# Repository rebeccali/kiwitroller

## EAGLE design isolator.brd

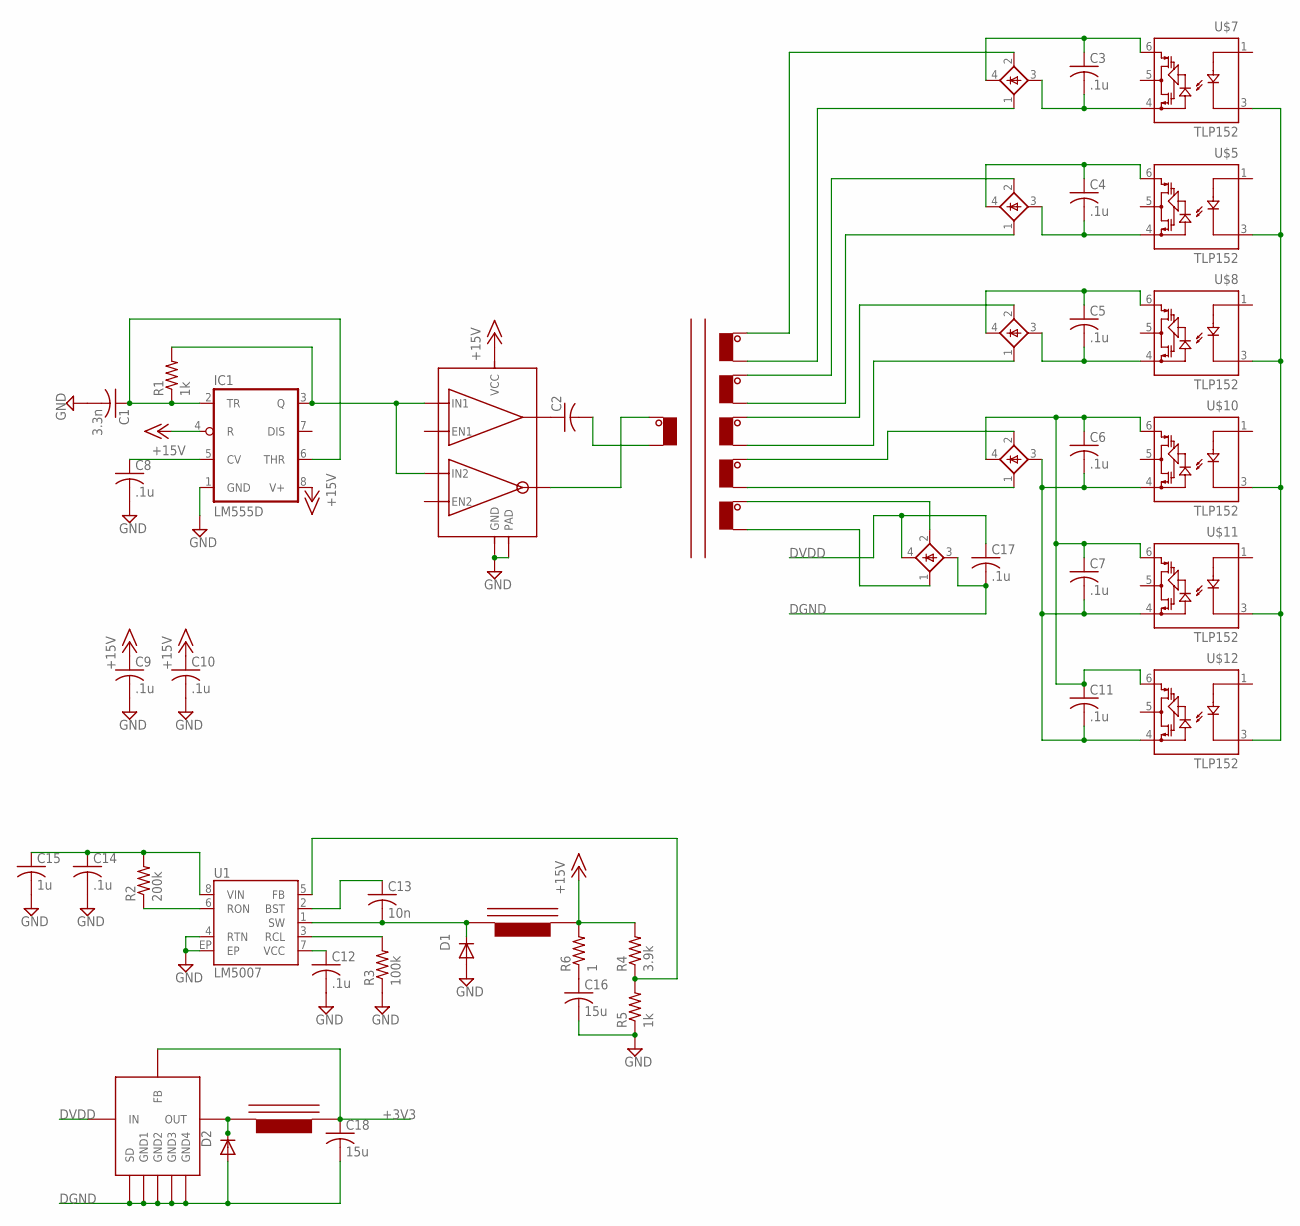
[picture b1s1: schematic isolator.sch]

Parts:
C1: 3.3n; C0805K
C2: C-USC0805K; C0805K
C3, C4, C5, C6, C7, C8, C9, C10, C11, C12, C14, C17: .1u; C0805K
C13: 10n; C0805K
C15: 1u; C0805K
C16, C18: 15u; C0805K
D1, D2: B170-13-F; DO214AC
IC1: LM555D; SO08
R1, R5: 1k; M0805
R2: 200k; M0805
R3: 100k; M0805
R4: 3.9k; M0805
R6: 1; M0805
U1: LM5007; MSOP-8-EP
U$1: HP1
U$2: UCC27525DGN; HTSSOP8DGN
U$3, U$4, U$6, U$9, U$14: BAS4002A; SOT-143
U$5, U$7, U$8, U$10, U$11, U$12: TLP152; DIP5-SMD
U$13, U$16: SRN6045-101M; SRN6045
U$15: AP1509; SO8

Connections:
+3V3: C18.1, U$15.3 (FB), U$16.P$2; also elsewhere on the board
+15V: C9.1, C10.1, IC1.4 (R), IC1.8 (V+), R4.2, R6.2, U$2.6 (VCC), U$13.P$2
DGND: C17.2, C18.2, D2.A, U$5.3 (LED-), U$7.3 (LED-), U$8.3 (LED-), U$10.3 (LED-), U$11.3 (LED-), U$12.3 (LED-), U$14.3 (-), U$15.4 (SD), U$15.5 (GND1), U$15.6 (GND2), U$15.7 (GND3), U$15.8 (GND4); also elsewhere on the board
DVDD: C17.1, U$14.4 (+), U$15.1 (IN)
E1: C3.2, U$3.3 (-), U$7.4 (GND); also elsewhere on the board
E2: C4.2, U$4.3 (-), U$5.4 (GND); also elsewhere on the board
E3: C5.2, U$6.3 (-), U$8.4 (GND); also elsewhere on the board
GND: C1.2, C8.2, C9.2, C10.2, C12.2, C14.2, C15.2, C16.2, D1.A, IC1.1 (GND), R3.1, R5.1, U1.4 (RTN), U1.EP, U$2.3 (GND), U$2.EXP (PAD); also elsewhere on the board
IN1: U$7.1 (LED+); also elsewhere on the board
IN2: U$5.1 (LED+); also elsewhere on the board
IN3: U$8.1 (LED+); also elsewhere on the board
IN4: U$10.1 (LED+); also elsewhere on the board
IN5: U$11.1 (LED+); also elsewhere on the board
IN6: U$12.1 (LED+); also elsewhere on the board
unnamed: U$1.P$3 (3B), U$3.1 (AC1)
unnamed: C3.1, U$3.4 (+), U$7.6 (VDD)
unnamed: C2.1, U$2.7 (OUT1)
unnamed: U$1.P$4 (1A), U$2.5 (OUT2)
unnamed: C1.1, IC1.2 (TR), IC1.6 (THR), R1.1
unnamed: U$1.P$10 (4A), U$4.2 (AC2)
unnamed: C8.1, IC1.5 (CV)
unnamed: IC1.3 (Q), R1.2, U$2.2 (IN1), U$2.4 (IN2)
unnamed: U$1.P$6 (3A), U$3.2 (AC2)
unnamed: U$1.P$7 (4B), U$4.1 (AC1)
unnamed: C4.1, U$4.4 (+), U$5.6 (VDD)
unnamed: U$1.P$11 (5A), U$6.2 (AC2)
unnamed: U$1.P$8 (5B), U$6.1 (AC1)
unnamed: C5.1, U$6.4 (+), U$8.6 (VDD)
unnamed: U$1.P$12 (6A), U$9.2 (AC2)
unnamed: U$1.P$9 (6B), U$9.1 (AC1)
unnamed: C16.1, R6.1
unnamed: U$1.P$5 (2A), U$14.2 (AC2)
unnamed: C6.1, C7.1, C11.1, U$9.4 (+), U$10.6 (VDD), U$11.6 (VDD), U$12.6 (VDD)
unnamed: R4.1, R5.2, U1.5 (FB)
unnamed: U$1.P$2 (2B), U$14.1 (AC1)
unnamed: R2.1, U1.6 (RON)
unnamed: D2.C, U$15.2 (OUT), U$16.P$1
unnamed: C2.2, U$1.P$1 (1B)
unnamed: C12.1, U1.7 (VCC)
unnamed: C13.2, D1.C, U1.1 (SW), U$13.P$1
unnamed: C13.1, U1.2 (BST)
unnamed: R3.2, U1.3 (RCL)
OUT1: U$7.5 (VO); also elsewhere on the board
OUT2: U$5.5 (VO); also elsewhere on the board
OUT3: U$8.5 (VO); also elsewhere on the board
OUT4: U$10.5 (VO); also elsewhere on the board
OUT5: U$11.5 (VO); also elsewhere on the board
OUT6: U$12.5 (VO); also elsewhere on the board
PGND: C6.2, C7.2, C11.2, U$9.3 (-), U$10.4 (GND), U$11.4 (GND), U$12.4 (GND); also elsewhere on the board
VIN: C14.1, C15.1, R2.2, U1.8 (VIN); also elsewhere on the board

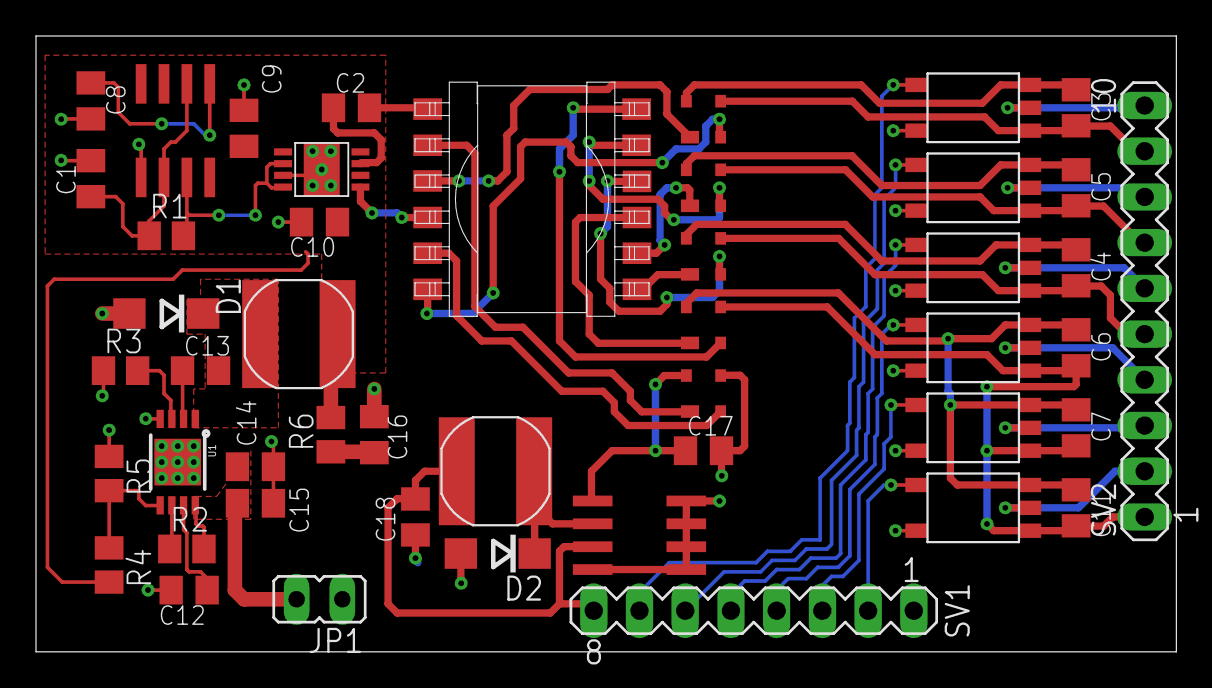
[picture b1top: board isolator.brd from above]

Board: 2 copper layers, 63.4 x 34.2 mm, 47 parts (0 on the bottom side), 50 nets.

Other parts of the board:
JP1: JP1
SV1: MA08-1
SV2: MA10-1

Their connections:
+3V3: SV1.8; also elsewhere on the board
DGND: SV1.1; also elsewhere on the board
E1: SV2.9; also elsewhere on the board
E2: SV2.5; also elsewhere on the board
E3: SV2.7; also elsewhere on the board
GND: JP1.1; also elsewhere on the board
IN1: SV1.7; also elsewhere on the board
IN2: SV1.5; also elsewhere on the board
IN3: SV1.6; also elsewhere on the board
IN4: SV1.4; also elsewhere on the board
IN5: SV1.3; also elsewhere on the board
IN6: SV1.2; also elsewhere on the board
OUT1: SV2.10; also elsewhere on the board
OUT2: SV2.6; also elsewhere on the board
OUT3: SV2.8; also elsewhere on the board
OUT4: SV2.4; also elsewhere on the board
OUT5: SV2.3; also elsewhere on the board
OUT6: SV2.2; also elsewhere on the board
PGND: SV2.1; also elsewhere on the board
VIN: JP1.2; also elsewhere on the board

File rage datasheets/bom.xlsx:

HP1-1400LD | 2.09 | 1 | 2.09 |  | 14.463270000000001
UCC27525DGN | 0.95062000000000002 | 1 | 0.95062000000000002
ICM7555 | 0.3135 | 1 | 0.3135
SRN6045 | 0.16320000000000001 | 1 | 0.16320000000000001
LM5007 | 1.4624999999999999 | 1 | 1.4624999999999999
BAS4002A | 0.14105000000000001 | 5 | 0.70525000000000004
B170-13-F | 0.21 | 1 | 0.21
TLP152 | 0.51870000000000005 | 6 | 3.1122000000000005
Passives | 0.04 | 23 | 0.92
IXDD609 | 0.75600000000000001 | 6 | 4.5359999999999996

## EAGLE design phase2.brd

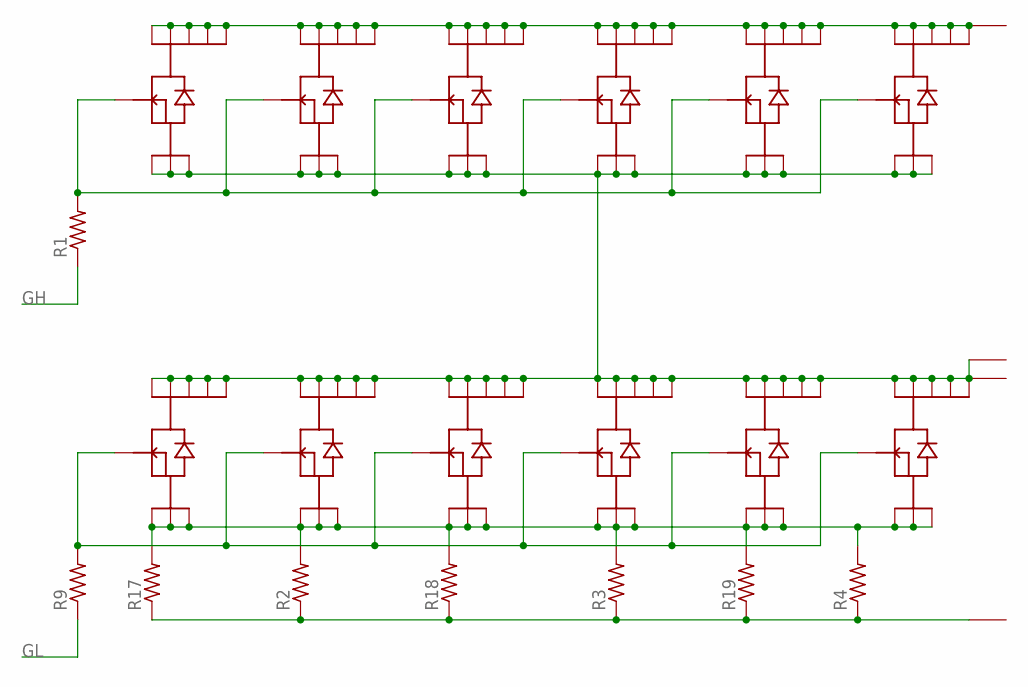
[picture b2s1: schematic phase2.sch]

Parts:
R1, R9: R-US_R1206; R1206
R2, R3, R4, R17, R18, R19: R-US_M1206; M1206
U$1, U$2, U$3, U$4, U$5, U$6, U$9, U$10, U$11, U$12, U$13, U$14: TPH2R608NH; SOP-ADVANCE
U$17, U$18, U$19: BUSBAR
U$20: POWERPAD

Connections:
GH: R1.1
GL: R9.1
unnamed: R1.2, U$1.4 (G), U$2.4 (G), U$3.4 (G), U$4.4 (G), U$5.4 (G), U$6.4 (G)
unnamed: R9.2, U$9.4 (G), U$10.4 (G), U$11.4 (G), U$12.4 (G), U$13.4 (G), U$14.4 (G)
unnamed: U$1.5 (D1), U$1.6 (D2), U$1.7 (D3), U$1.8 (D4), U$1.9 (DTAB), U$2.5 (D1), U$2.6 (D2), U$2.7 (D3), U$2.8 (D4), U$2.9 (DTAB), U$3.5 (D1), U$3.6 (D2), U$3.7 (D3), U$3.8 (D4), U$3.9 (DTAB), U$4.5 (D1), U$4.6 (D2), U$4.7 (D3), U$4.8 (D4), U$4.9 (DTAB), U$5.5 (D1), U$5.6 (D2), U$5.7 (D3), U$5.8 (D4), U$5.9 (DTAB), U$6.5 (D1), U$6.6 (D2), U$6.7 (D3), U$6.8 (D4), U$6.9 (DTAB), U$17.P$1
unnamed: R2.1, R3.1, R4.1, R17.1, R18.1, R19.1, U$19.P$1
unnamed: U$1.1 (S1), U$1.2 (S2), U$1.3 (S3), U$2.1 (S1), U$2.2 (S2), U$2.3 (S3), U$3.1 (S1), U$3.2 (S2), U$3.3 (S3), U$4.1 (S1), U$4.2 (S2), U$4.3 (S3), U$5.1 (S1), U$5.2 (S2), U$5.3 (S3), U$6.1 (S1), U$6.2 (S2), U$6.3 (S3), U$9.5 (D1), U$9.6 (D2), U$9.7 (D3), U$9.8 (D4), U$9.9 (DTAB), U$10.5 (D1), U$10.6 (D2), U$10.7 (D3), U$10.8 (D4), U$10.9 (DTAB), U$11.5 (D1), U$11.6 (D2), U$11.7 (D3), U$11.8 (D4), U$11.9 (DTAB), U$12.5 (D1), U$12.6 (D2), U$12.7 (D3), U$12.8 (D4), U$12.9 (DTAB), U$13.5 (D1), U$13.6 (D2), U$13.7 (D3), U$13.8 (D4), U$13.9 (DTAB), U$14.5 (D1), U$14.6 (D2), U$14.7 (D3), U$14.8 (D4), U$14.9 (DTAB), U$18.P$1, U$20.P$1
unnamed: R2.2, R3.2, R4.2, R17.2, R18.2, R19.2, U$9.1 (S1), U$9.2 (S2), U$9.3 (S3), U$10.1 (S1), U$10.2 (S2), U$10.3 (S3), U$11.1 (S1), U$11.2 (S2), U$11.3 (S3), U$12.1 (S1), U$12.2 (S2), U$12.3 (S3), U$13.1 (S1), U$13.2 (S2), U$13.3 (S3), U$14.1 (S1), U$14.2 (S2), U$14.3 (S3)

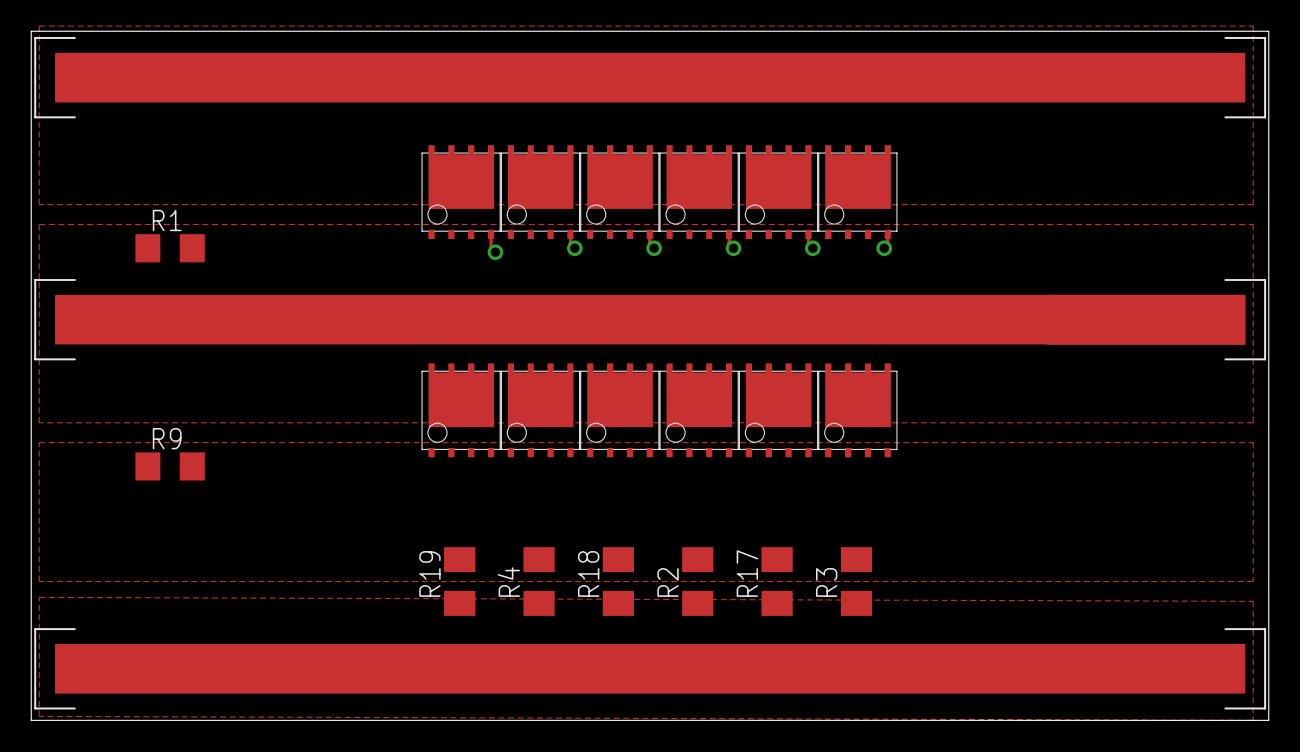
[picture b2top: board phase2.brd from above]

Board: 2 copper layers, 79.2 x 44.1 mm, 24 parts (0 on the bottom side), 6 nets.

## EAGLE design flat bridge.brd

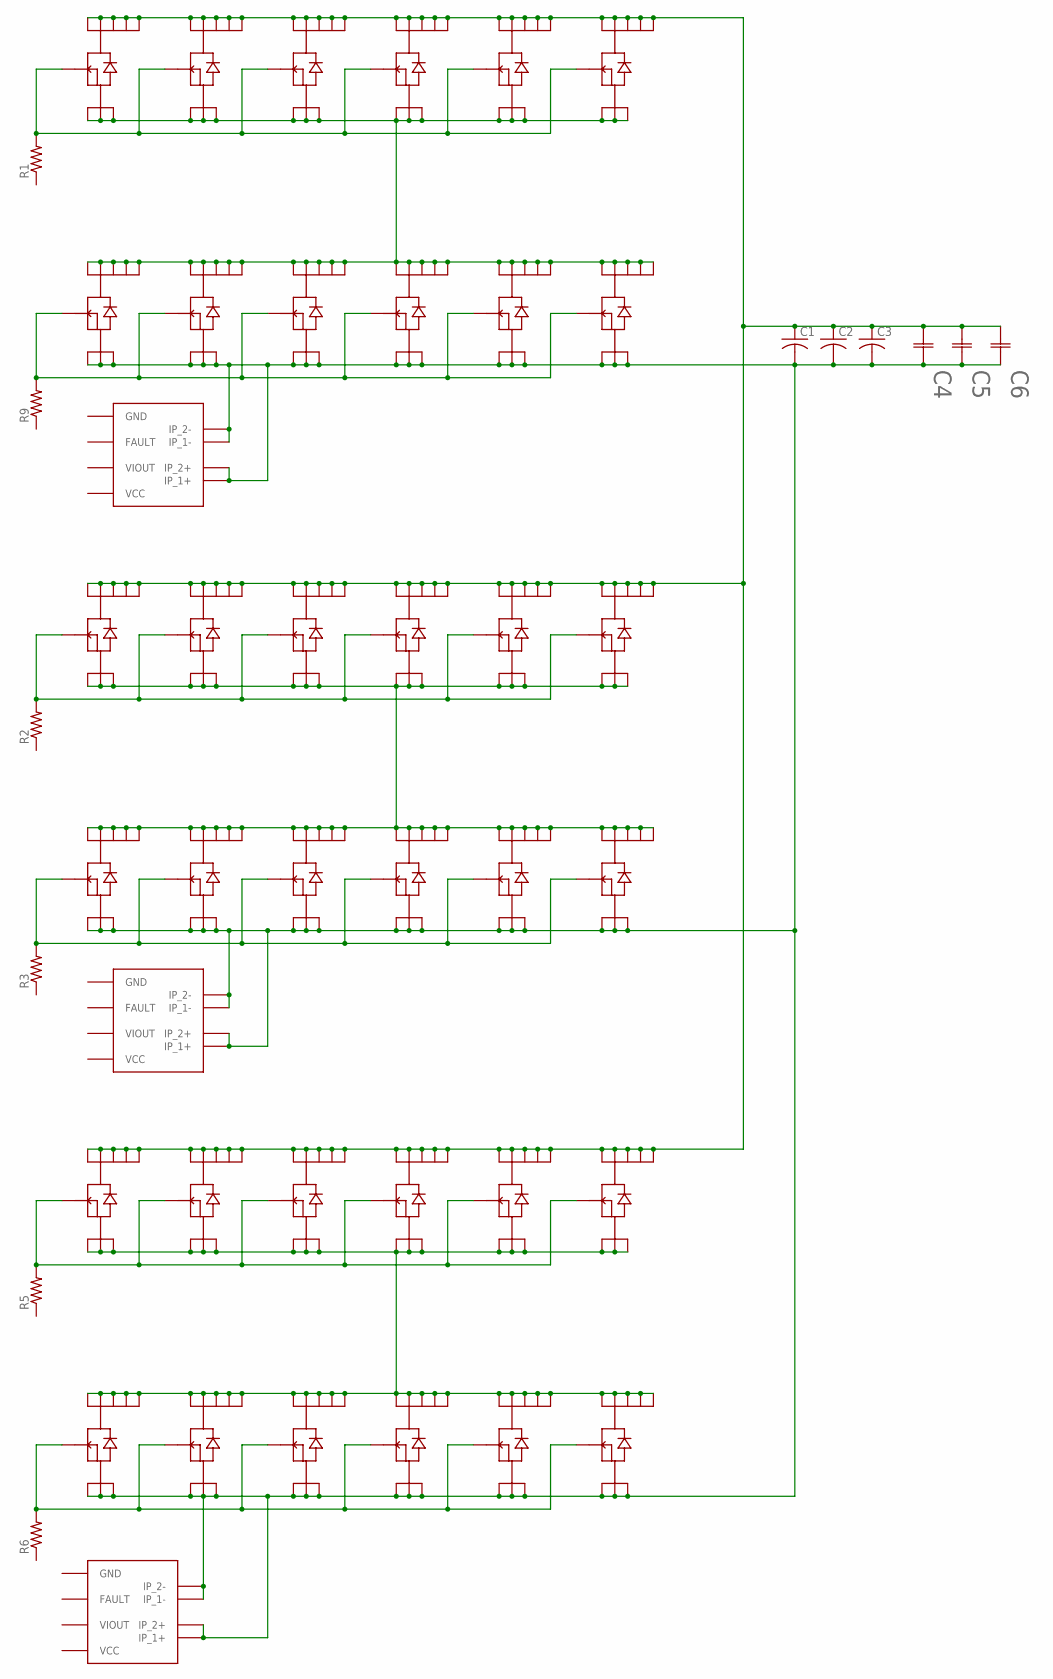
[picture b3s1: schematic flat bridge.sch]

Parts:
C1, C2, C3: C-USC2220K; C2220K
C4, C5, C6: EEVFK1J471M; CAP_EEFK_J16
R1, R2, R3, R5, R6, R9: R-US_R1206; R1206
U$1, U$2, U$3, U$4, U$5, U$6, U$8, U$9, U$10, U$11, U$12, U$13, U$14, U$15, U$16, U$17, U$18, U$19, U$21, U$22, U$23, U$24, U$25, U$26, U$29, U$30, U$31, U$32, U$33, U$34, U$35, U$36, U$37, U$38, U$39, U$40: TPH2R608NH; SOP-ADVANCE
U$7, U$28, U$42: ACS711; SO8

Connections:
unnamed: R1.2, U$1.4 (G), U$2.4 (G), U$3.4 (G), U$4.4 (G), U$5.4 (G), U$6.4 (G)
unnamed: C1.1, C2.1, C3.1, C4.1 (11), C5.1 (11), C6.1 (11), U$1.5 (D1), U$1.6 (D2), U$1.7 (D3), U$1.8 (D4), U$1.9 (DTAB), U$2.5 (D1), U$2.6 (D2), U$2.7 (D3), U$2.8 (D4), U$2.9 (DTAB), U$3.5 (D1), U$3.6 (D2), U$3.7 (D3), U$3.8 (D4), U$3.9 (DTAB), U$4.5 (D1), U$4.6 (D2), U$4.7 (D3), U$4.8 (D4), U$4.9 (DTAB), U$5.5 (D1), U$5.6 (D2), U$5.7 (D3), U$5.8 (D4), U$5.9 (DTAB), U$6.5 (D1), U$6.6 (D2), U$6.7 (D3), U$6.8 (D4), U$6.9 (DTAB), U$8.5 (D1), U$8.6 (D2), U$8.7 (D3), U$8.8 (D4), U$8.9 (DTAB), U$15.5 (D1), U$15.6 (D2), U$15.7 (D3), U$15.8 (D4), U$15.9 (DTAB), U$16.5 (D1), U$16.6 (D2), U$16.7 (D3), U$16.8 (D4), U$16.9 (DTAB), U$17.5 (D1), U$17.6 (D2), U$17.7 (D3), U$17.8 (D4), U$17.9 (DTAB), U$18.5 (D1), U$18.6 (D2), U$18.7 (D3), U$18.8 (D4), U$18.9 (DTAB), U$19.5 (D1), U$19.6 (D2), U$19.7 (D3), U$19.8 (D4), U$19.9 (DTAB), U$29.5 (D1), U$29.6 (D2), U$29.7 (D3), U$29.8 (D4), U$29.9 (DTAB), U$30.5 (D1), U$30.6 (D2), U$30.7 (D3), U$30.8 (D4), U$30.9 (DTAB), U$31.5 (D1), U$31.6 (D2), U$31.7 (D3), U$31.8 (D4), U$31.9 (DTAB), U$32.5 (D1), U$32.6 (D2), U$32.7 (D3), U$32.8 (D4), U$32.9 (DTAB), U$33.5 (D1), U$33.6 (D2), U$33.7 (D3), U$33.8 (D4), U$33.9 (DTAB), U$34.5 (D1), U$34.6 (D2), U$34.7 (D3), U$34.8 (D4), U$34.9 (DTAB)
unnamed: R9.2, U$9.4 (G), U$10.4 (G), U$11.4 (G), U$12.4 (G), U$13.4 (G), U$14.4 (G)
unnamed: R2.2, U$8.4 (G), U$15.4 (G), U$16.4 (G), U$17.4 (G), U$18.4 (G), U$19.4 (G)
unnamed: U$8.1 (S1), U$8.2 (S2), U$8.3 (S3), U$15.1 (S1), U$15.2 (S2), U$15.3 (S3), U$16.1 (S1), U$16.2 (S2), U$16.3 (S3), U$17.1 (S1), U$17.2 (S2), U$17.3 (S3), U$18.1 (S1), U$18.2 (S2), U$18.3 (S3), U$19.1 (S1), U$19.2 (S2), U$19.3 (S3), U$21.5 (D1), U$21.6 (D2), U$21.7 (D3), U$21.8 (D4), U$21.9 (DTAB), U$22.5 (D1), U$22.6 (D2), U$22.7 (D3), U$22.8 (D4), U$22.9 (DTAB), U$23.5 (D1), U$23.6 (D2), U$23.7 (D3), U$23.8 (D4), U$23.9 (DTAB), U$24.5 (D1), U$24.6 (D2), U$24.7 (D3), U$24.8 (D4), U$24.9 (DTAB), U$25.5 (D1), U$25.6 (D2), U$25.7 (D3), U$25.8 (D4), U$25.9 (DTAB), U$26.5 (D1), U$26.6 (D2), U$26.7 (D3), U$26.8 (D4), U$26.9 (DTAB)
unnamed: R3.2, U$21.4 (G), U$22.4 (G), U$23.4 (G), U$24.4 (G), U$25.4 (G), U$26.4 (G)
unnamed: R5.2, U$29.4 (G), U$30.4 (G), U$31.4 (G), U$32.4 (G), U$33.4 (G), U$34.4 (G)
unnamed: U$29.1 (S1), U$29.2 (S2), U$29.3 (S3), U$30.1 (S1), U$30.2 (S2), U$30.3 (S3), U$31.1 (S1), U$31.2 (S2), U$31.3 (S3), U$32.1 (S1), U$32.2 (S2), U$32.3 (S3), U$33.1 (S1), U$33.2 (S2), U$33.3 (S3), U$34.1 (S1), U$34.2 (S2), U$34.3 (S3), U$35.5 (D1), U$35.6 (D2), U$35.7 (D3), U$35.8 (D4), U$35.9 (DTAB), U$36.5 (D1), U$36.6 (D2), U$36.7 (D3), U$36.8 (D4), U$36.9 (DTAB), U$37.5 (D1), U$37.6 (D2), U$37.7 (D3), U$37.8 (D4), U$37.9 (DTAB), U$38.5 (D1), U$38.6 (D2), U$38.7 (D3), U$38.8 (D4), U$38.9 (DTAB), U$39.5 (D1), U$39.6 (D2), U$39.7 (D3), U$39.8 (D4), U$39.9 (DTAB), U$40.5 (D1), U$40.6 (D2), U$40.7 (D3), U$40.8 (D4), U$40.9 (DTAB)
unnamed: C1.2, C2.2, C3.2, C4.2 (22), C5.2 (22), C6.2 (22), U$7.1 (IP_1+), U$7.2 (IP_2+), U$7.3 (IP_1-), U$7.4 (IP_2-), U$9.1 (S1), U$9.2 (S2), U$9.3 (S3), U$10.1 (S1), U$10.2 (S2), U$10.3 (S3), U$11.1 (S1), U$11.2 (S2), U$11.3 (S3), U$12.1 (S1), U$12.2 (S2), U$12.3 (S3), U$13.1 (S1), U$13.2 (S2), U$13.3 (S3), U$14.1 (S1), U$14.2 (S2), U$14.3 (S3), U$21.1 (S1), U$21.2 (S2), U$21.3 (S3), U$22.1 (S1), U$22.2 (S2), U$22.3 (S3), U$23.1 (S1), U$23.2 (S2), U$23.3 (S3), U$24.1 (S1), U$24.2 (S2), U$24.3 (S3), U$25.1 (S1), U$25.2 (S2), U$25.3 (S3), U$26.1 (S1), U$26.2 (S2), U$26.3 (S3), U$28.1 (IP_1+), U$28.2 (IP_2+), U$28.3 (IP_1-), U$28.4 (IP_2-), U$35.1 (S1), U$35.2 (S2), U$35.3 (S3), U$36.1 (S1), U$36.2 (S2), U$36.3 (S3), U$37.1 (S1), U$37.2 (S2), U$37.3 (S3), U$38.1 (S1), U$38.2 (S2), U$38.3 (S3), U$39.1 (S1), U$39.2 (S2), U$39.3 (S3), U$40.1 (S1), U$40.2 (S2), U$40.3 (S3), U$42.1 (IP_1+), U$42.2 (IP_2+), U$42.3 (IP_1-), U$42.4 (IP_2-)
unnamed: R6.2, U$35.4 (G), U$36.4 (G), U$37.4 (G), U$38.4 (G), U$39.4 (G), U$40.4 (G)
unnamed: U$1.1 (S1), U$1.2 (S2), U$1.3 (S3), U$2.1 (S1), U$2.2 (S2), U$2.3 (S3), U$3.1 (S1), U$3.2 (S2), U$3.3 (S3), U$4.1 (S1), U$4.2 (S2), U$4.3 (S3), U$5.1 (S1), U$5.2 (S2), U$5.3 (S3), U$6.1 (S1), U$6.2 (S2), U$6.3 (S3), U$9.5 (D1), U$9.6 (D2), U$9.7 (D3), U$9.8 (D4), U$9.9 (DTAB), U$10.5 (D1), U$10.6 (D2), U$10.7 (D3), U$10.8 (D4), U$10.9 (DTAB), U$11.5 (D1), U$11.6 (D2), U$11.7 (D3), U$11.8 (D4), U$11.9 (DTAB), U$12.5 (D1), U$12.6 (D2), U$12.7 (D3), U$12.8 (D4), U$12.9 (DTAB), U$13.5 (D1), U$13.6 (D2), U$13.7 (D3), U$13.8 (D4), U$13.9 (DTAB), U$14.5 (D1), U$14.6 (D2), U$14.7 (D3), U$14.8 (D4), U$14.9 (DTAB)

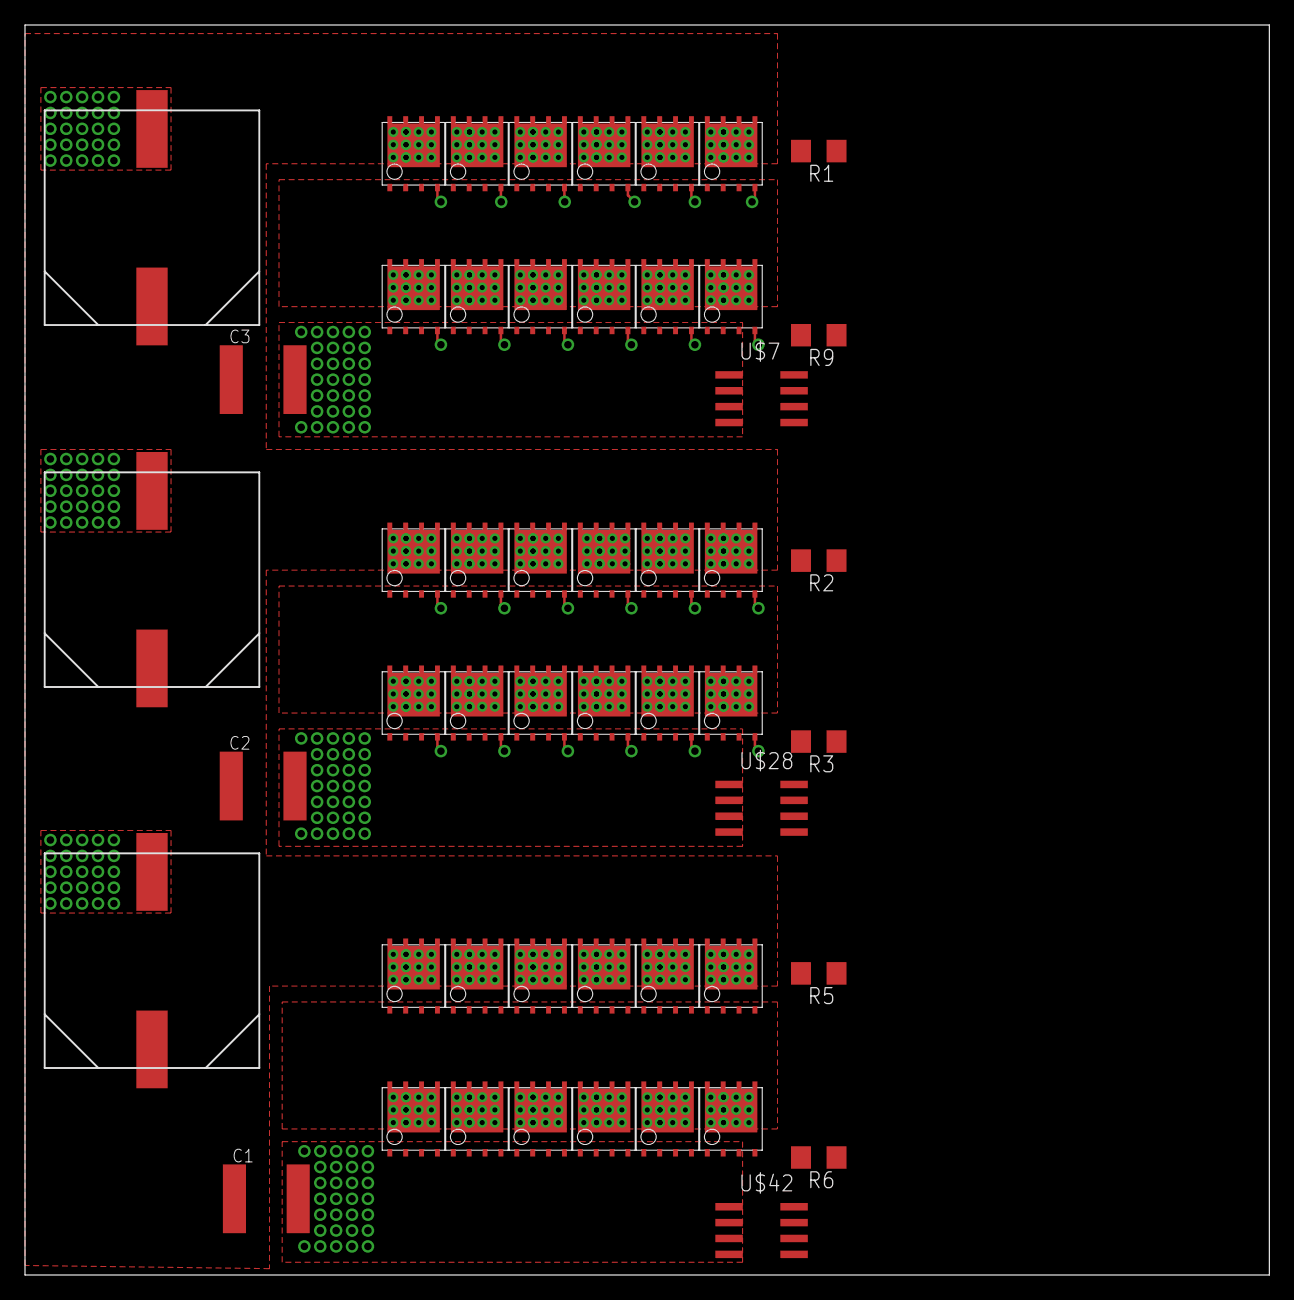
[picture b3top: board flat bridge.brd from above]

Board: 2 copper layers, 99.5 x 100.0 mm, 51 parts (0 on the bottom side), 11 nets.

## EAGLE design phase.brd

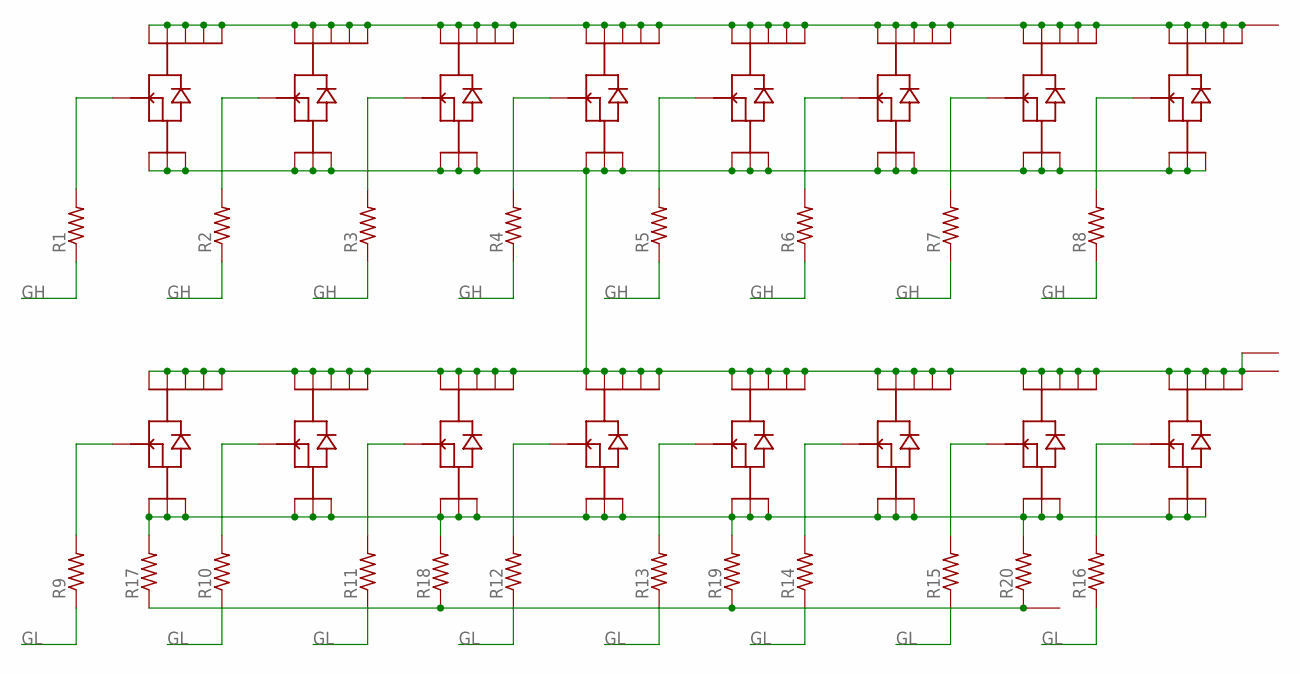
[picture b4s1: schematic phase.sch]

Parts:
R1, R2, R3, R4, R5, R6, R7, R8, R9, R10, R11, R12, R13, R14, R15, R16: R-US_R0603; R0603
R17, R18, R19, R20: R-US_M1206; M1206
U$1, U$2, U$3, U$4, U$5, U$6, U$7, U$8, U$9, U$10, U$11, U$12, U$13, U$14, U$15, U$16: TPH2R608NH; SOP-ADVANCE
U$17, U$18, U$19: BUSBAR
U$20: POWERPAD

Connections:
GH: R1.1, R2.1, R3.1, R4.1, R5.1, R6.1, R7.1, R8.1
GL: R9.1, R10.1, R11.1, R12.1, R13.1, R14.1, R15.1, R16.1
unnamed: R1.2, U$1.4 (G)
unnamed: R2.2, U$2.4 (G)
unnamed: R3.2, U$3.4 (G)
unnamed: R4.2, U$4.4 (G)
unnamed: R5.2, U$5.4 (G)
unnamed: R6.2, U$6.4 (G)
unnamed: R7.2, U$7.4 (G)
unnamed: R8.2, U$8.4 (G)
unnamed: R9.2, U$9.4 (G)
unnamed: R10.2, U$10.4 (G)
unnamed: R11.2, U$11.4 (G)
unnamed: R12.2, U$12.4 (G)
unnamed: R13.2, U$13.4 (G)
unnamed: R14.2, U$14.4 (G)
unnamed: R15.2, U$15.4 (G)
unnamed: R16.2, U$16.4 (G)
unnamed: U$1.5 (D1), U$1.6 (D2), U$1.7 (D3), U$1.8 (D4), U$1.9 (DTAB), U$2.5 (D1), U$2.6 (D2), U$2.7 (D3), U$2.8 (D4), U$2.9 (DTAB), U$3.5 (D1), U$3.6 (D2), U$3.7 (D3), U$3.8 (D4), U$3.9 (DTAB), U$4.5 (D1), U$4.6 (D2), U$4.7 (D3), U$4.8 (D4), U$4.9 (DTAB), U$5.5 (D1), U$5.6 (D2), U$5.7 (D3), U$5.8 (D4), U$5.9 (DTAB), U$6.5 (D1), U$6.6 (D2), U$6.7 (D3), U$6.8 (D4), U$6.9 (DTAB), U$7.5 (D1), U$7.6 (D2), U$7.7 (D3), U$7.8 (D4), U$7.9 (DTAB), U$8.5 (D1), U$8.6 (D2), U$8.7 (D3), U$8.8 (D4), U$8.9 (DTAB), U$17.P$1
unnamed: R17.1, R18.1, R19.1, R20.1, U$19.P$1
unnamed: U$1.1 (S1), U$1.2 (S2), U$1.3 (S3), U$2.1 (S1), U$2.2 (S2), U$2.3 (S3), U$3.1 (S1), U$3.2 (S2), U$3.3 (S3), U$4.1 (S1), U$4.2 (S2), U$4.3 (S3), U$5.1 (S1), U$5.2 (S2), U$5.3 (S3), U$6.1 (S1), U$6.2 (S2), U$6.3 (S3), U$7.1 (S1), U$7.2 (S2), U$7.3 (S3), U$8.1 (S1), U$8.2 (S2), U$8.3 (S3), U$9.5 (D1), U$9.6 (D2), U$9.7 (D3), U$9.8 (D4), U$9.9 (DTAB), U$10.5 (D1), U$10.6 (D2), U$10.7 (D3), U$10.8 (D4), U$10.9 (DTAB), U$11.5 (D1), U$11.6 (D2), U$11.7 (D3), U$11.8 (D4), U$11.9 (DTAB), U$12.5 (D1), U$12.6 (D2), U$12.7 (D3), U$12.8 (D4), U$12.9 (DTAB), U$13.5 (D1), U$13.6 (D2), U$13.7 (D3), U$13.8 (D4), U$13.9 (DTAB), U$14.5 (D1), U$14.6 (D2), U$14.7 (D3), U$14.8 (D4), U$14.9 (DTAB), U$15.5 (D1), U$15.6 (D2), U$15.7 (D3), U$15.8 (D4), U$15.9 (DTAB), U$16.5 (D1), U$16.6 (D2), U$16.7 (D3), U$16.8 (D4), U$16.9 (DTAB), U$18.P$1, U$20.P$1
unnamed: R17.2, R18.2, R19.2, R20.2, U$9.1 (S1), U$9.2 (S2), U$9.3 (S3), U$10.1 (S1), U$10.2 (S2), U$10.3 (S3), U$11.1 (S1), U$11.2 (S2), U$11.3 (S3), U$12.1 (S1), U$12.2 (S2), U$12.3 (S3), U$13.1 (S1), U$13.2 (S2), U$13.3 (S3), U$14.1 (S1), U$14.2 (S2), U$14.3 (S3), U$15.1 (S1), U$15.2 (S2), U$15.3 (S3), U$16.1 (S1), U$16.2 (S2), U$16.3 (S3)

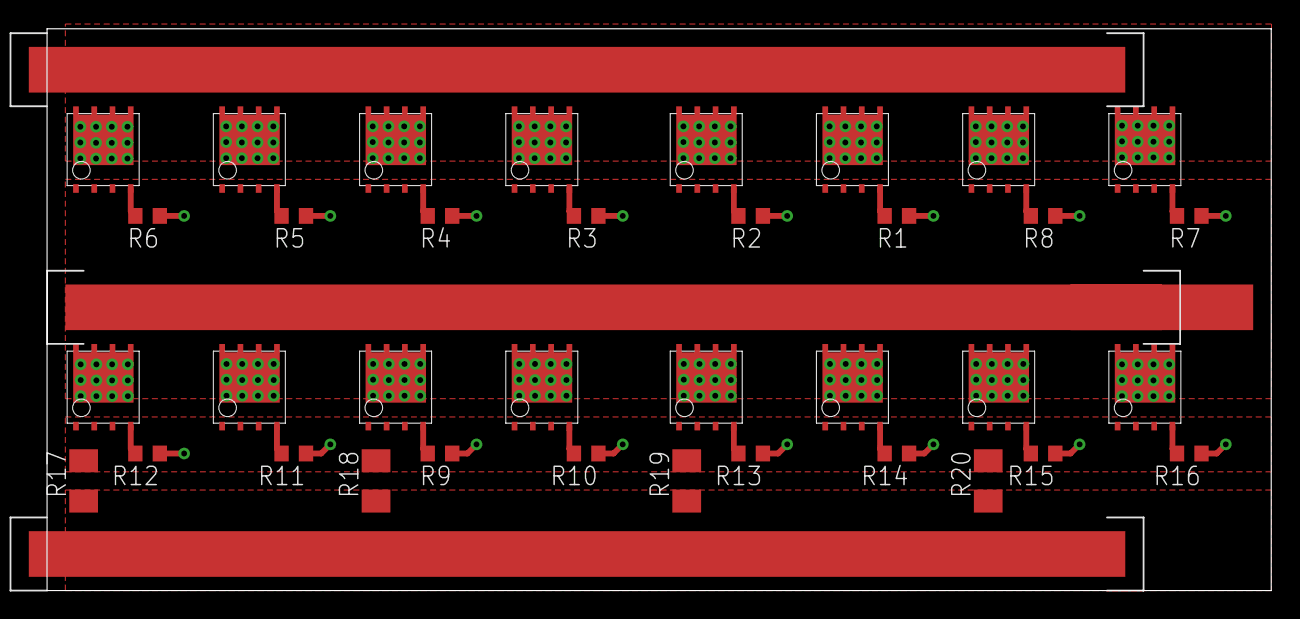
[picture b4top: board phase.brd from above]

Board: 2 copper layers, 85.1 x 39.0 mm, 40 parts (0 on the bottom side), 22 nets.

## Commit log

2016-05-27 :neckbeard: Added .gitattributes & .gitignore files
2016-05-27 inital upload of bridge layout ideas, etc
2016-05-27 added datasheets
2016-05-28 added sk3 solidworks model
2016-05-29 new isolator design
2016-05-29 BOM spreadsheet, new isolator parts
2016-05-29 Added names to some parts, still missing some lbrs for some parts on stuff, including isolator.sch
2016-05-30 up-to-date brushlessrage.lbr, updated isolator for send-out
2016-05-31 fixed drc errors on isolator.brd
2016-05-31 added Eagle project file
2016-06-13 Adding STM32 - not quite complete addition to lbr
    don't use it!
2016-06-20 added in stm32 chip forealz
2016-07-10 augh
2016-07-10 Extracted Cheetah sch to lbr
    yep
2016-07-10 added in micro with vague connections
2016-07-10 adding some caps

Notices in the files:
parts and their libraries:
COPYRIGHT: Copyright (C) 2015 Accelerated Designs. All rights reserved
SparkFun-PowerIC: Licensing: Creative Commons ShareAlike 4.0 International - https://creativecommons.org/licenses/by-sa/4.0
